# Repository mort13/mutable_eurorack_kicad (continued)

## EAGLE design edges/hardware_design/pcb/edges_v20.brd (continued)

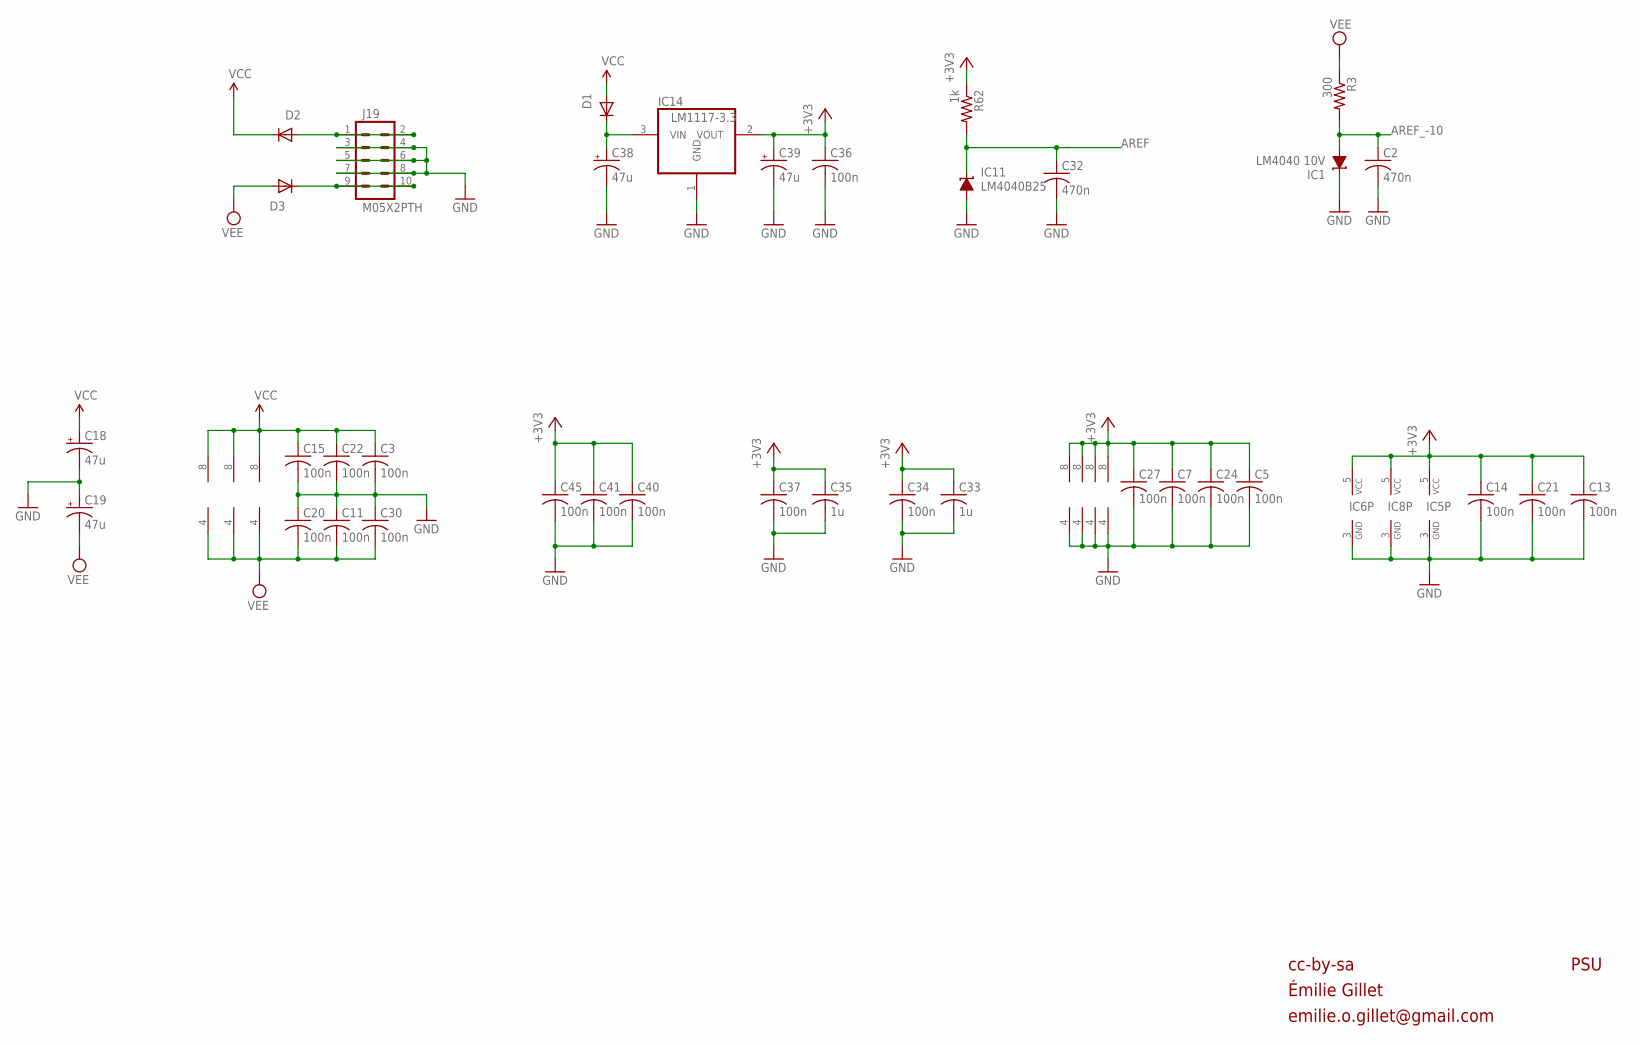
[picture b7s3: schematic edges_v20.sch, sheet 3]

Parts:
C2, C32: 470n; C0603
C3, C5, C7, C11, C13, C14, C15, C20, C21, C22, C24, C27, C30, C34, C36, C37, C40, C41, C45: 100n; C0603
C18, C19, C38, C39: 47u; PANASONIC_D
C33, C35: 1u; C0603
D1, D2, D3: 1N5819HW; SOD123
IC1: LM4040 10V; DBZ_R-PDSO-G3
IC2, IC7, IC9: TL072D; SO08
IC3, IC4, IC10, IC12: MCP6002; SO08
IC5: 74AHC1G125DBV; SOT23-5
IC6, IC8: 74AHC1G86DBV; SOT23-5
IC11: LM4040B25; DBZ_R-PDSO-G3
IC14: LM1117-3.3; SOT223
J19: M05X2PTH; AVR_ICSP
R3: 300; R0603
R62: 1k; R0603

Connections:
+3V3: C5.1, C7.1, C13.1, C14.1, C21.1, C24.1, C27.1, C33.1, C34.1, C35.1, C36.1, C37.1, C39.+, C40.1, C41.1, C45.1, IC3.8 (V+), IC4.8 (V+), IC5.5 (VCC), IC6.5 (VCC), IC8.5 (VCC), IC10.8 (V+), IC12.8 (V+), IC14.2 (VOUT), R62.1; also elsewhere on the board
AREF: C32.1, IC11.1 (C), R62.2; also elsewhere on the board
AREF_-10: C2.1, IC1.2 (A), R3.2; also elsewhere on the board
GND: C2.2, C3.2, C5.2, C7.2, C11.1, C13.2, C14.2, C15.2, C18.-, C19.+, C20.1, C21.2, C22.2, C24.2, C27.2, C30.1, C32.2, C33.2, C34.2, C35.2, C36.2, C37.2, C38.-, C39.-, C40.2, C41.2, C45.2, IC1.1 (C), IC3.4 (V-), IC4.4 (V-), IC5.3 (GND), IC6.3 (GND), IC8.3 (GND), IC10.4 (V-), IC11.2 (A), IC12.4 (V-), IC14.1 (GND), J19.3, J19.4, J19.5, J19.6, J19.7, J19.8; also elsewhere on the board
unnamed: C38.+, D1.C, IC14.3 (VIN)
unnamed: D2.A, J19.1, J19.2
unnamed: D3.C, J19.9, J19.10
VCC: C3.1, C15.1, C18.+, C22.1, D1.A, D2.C, IC2.8 (V+), IC7.8 (V+), IC9.8 (V+); also elsewhere on the board
VEE: C11.2, C19.-, C20.2, C30.2, D3.A, IC2.4 (V-), IC7.4 (V-), IC9.4 (V-), R3.1

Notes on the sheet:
cc-by-sa
PSU
Émilie Gillet
emilie.o.gillet@gmail.com

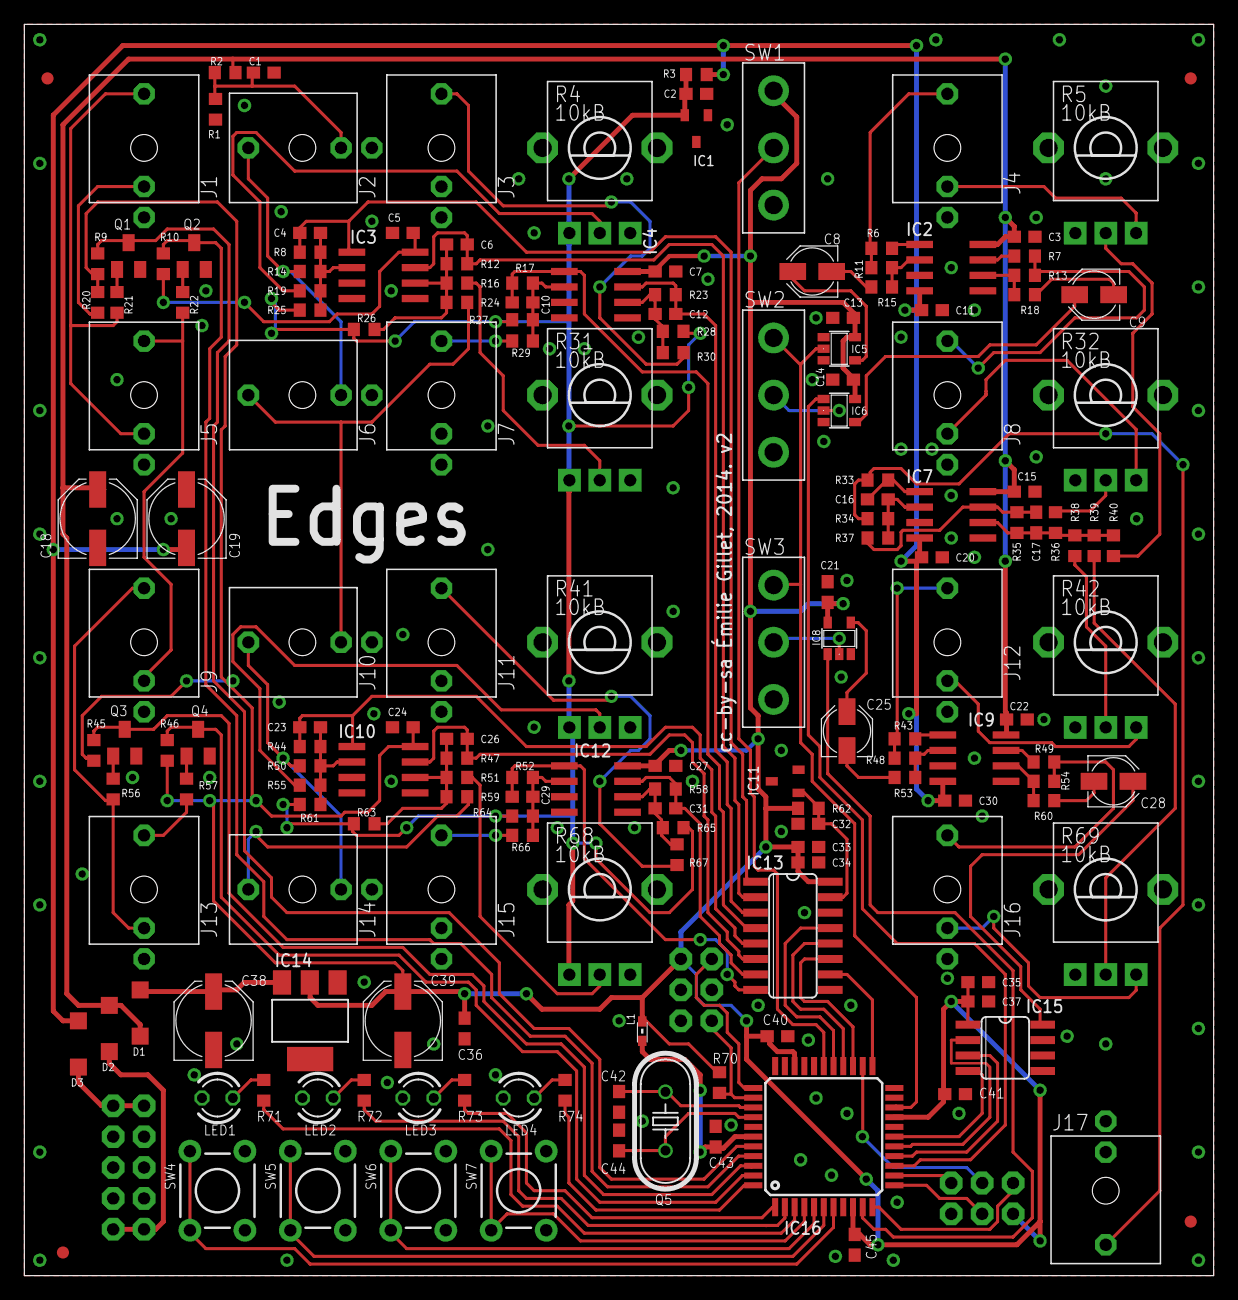
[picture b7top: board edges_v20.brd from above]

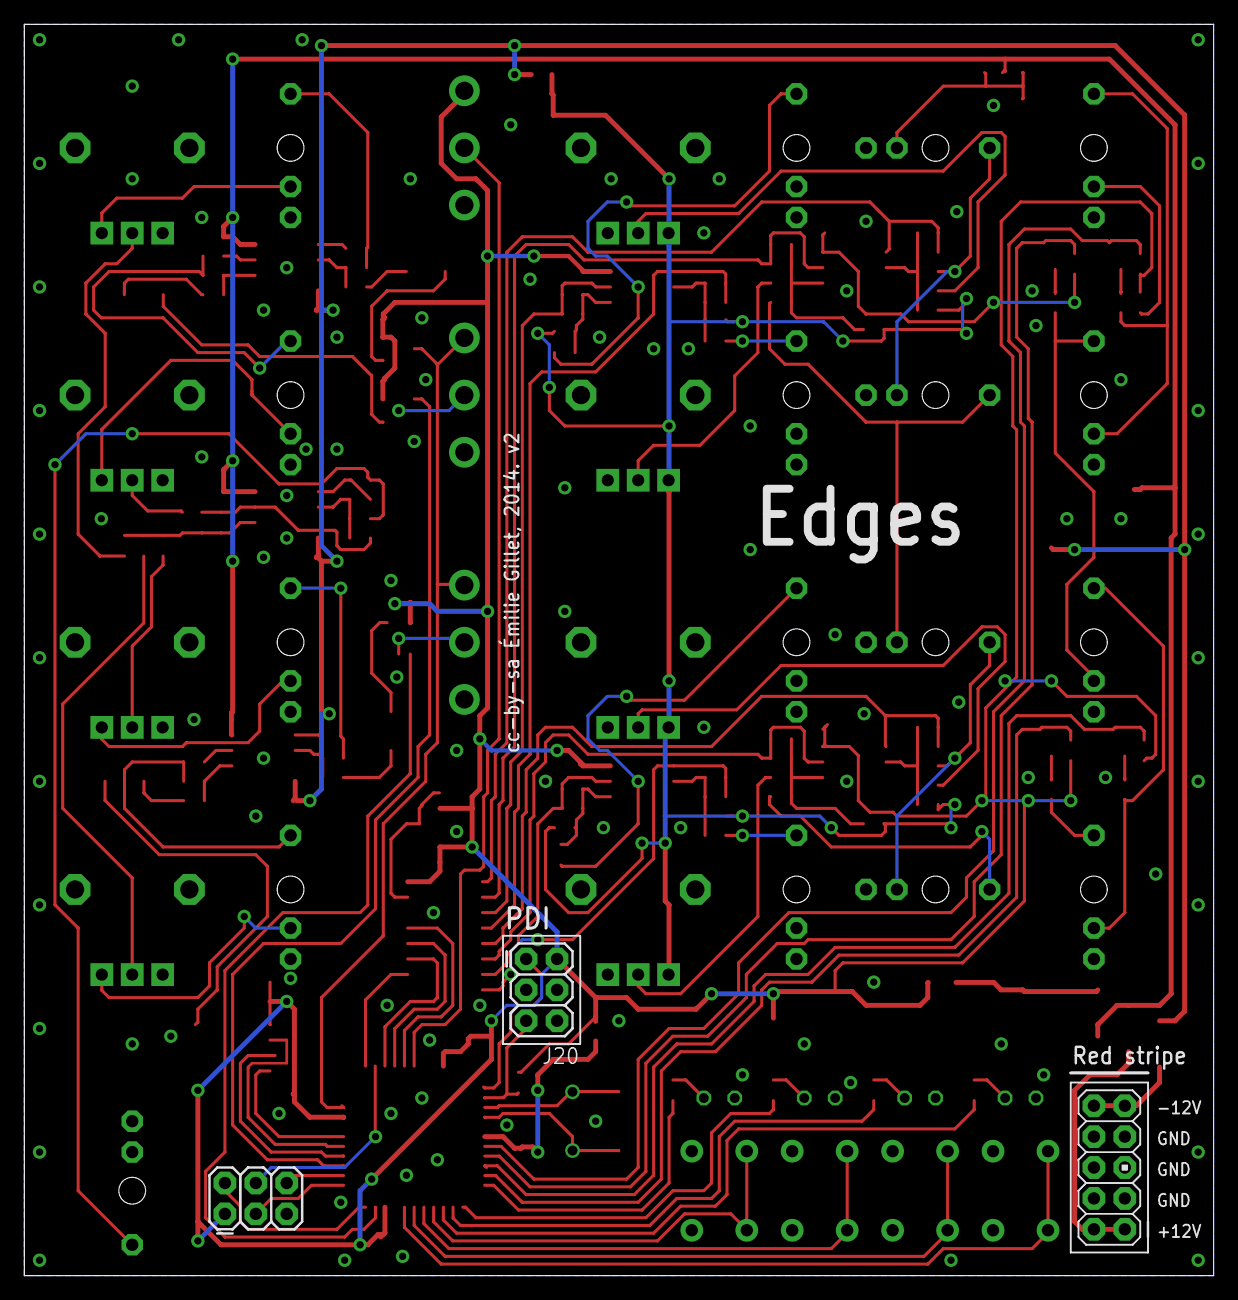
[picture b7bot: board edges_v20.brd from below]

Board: 2 copper layers, 97.8 x 102.9 mm, 179 parts (3 on the bottom side), 118 nets.

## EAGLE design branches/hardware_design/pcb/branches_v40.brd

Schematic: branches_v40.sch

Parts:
C1, C4, C6, C7, C8: 100n; C0603
C2, C5: 1n; C0603
C3, C9: 22u; PANASONIC_C
D1: 1N5819HW; SOD123
F1, F2, F3, F4: FIDUCIAL1X2; FIDUCIAL-1X2
IC1: LM4040 5.0V; DBZ_R-PDSO-G3
IC2: LM1117-5.0; SOT223
IC3: MCP6002; SO08
IC4: ATMEGA88PA-AU; TQFP32-08
J1, J2, J3, J4, J5, J6, J7, J8: PJ301_THONKICONN6; WQP_PJ_301M6
J9: AVR_SPI_PRG_6PTH; 2X3
J10: M05X2PTH; AVR_ICSP
L1: WE-CBF_0603; 0603
LED1, LED2: WP937EGW; LED3MM
Q1, Q2: MMBT3904; SOT23-BEC
R1, R2, R14: 10k; R0603
R3, R4, R5, R7, R8, R9, R10, R18: 100k; R0603
R6, R15: 10kB; ALPS_POT_VERTICAL_PS
R11, R19: 220; R0603
R12, R13, R16, R17: 1.0k; R0603
SW1, SW2: TAC_SWITCHPTH; TACTILE-PTH

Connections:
+5V: C1.1, C3.+, C4.1, C6.1, IC2.2 (VOUT), IC3.8 (V+), IC4.4 (VCC), IC4.6 (VCC), J9.2, L1.1, R14.2
AREF: C7.1, IC4.20 (AREF)
GATE1_IN: J1.P3 (3), J5.P2 (2), R10.2
GATE2_IN: J5.P3 (3), R18.2
GND: C1.2, C3.-, C4.2, C6.2, C7.2, C8.2, C9.-, IC1.1 (C), IC2.1 (GND), IC3.3 (+IN), IC3.4 (V-), IC3.5 (+IN), IC4.3 (GND), IC4.5 (AGND), IC4.21 (GND), J1.P1 (1), J1.P2 (2), J2.P1 (1), J3.P1 (1), J4.P1 (1), J5.P1 (1), J6.P1 (1), J7.P1 (1), J8.P1 (1), J9.6, J10.3, J10.4, J10.5, J10.6, J10.7, J10.8, Q1.E, Q2.E, R6.P$1 (E), R15.P$1 (E), SW1.1, SW1.2, SW2.1, SW2.2
IN1: IC4.2 (PD4(XCK/T0)), Q1.C
IN2: IC4.11 (PD7(AIN1)), Q2.C
MISO: IC4.16 (PB4(MISO)), J9.1
MOSI: IC4.15 (PB3(MOSI/OC2)), J9.4
unnamed: Q1.B, R10.1
unnamed: Q2.B, R18.1
unnamed: D1.A, J10.1
unnamed: C5.1, IC3.2 (-IN), R7.2, R8.2, R9.1
unnamed: J8.P3 (3), R16.2
unnamed: R7.1, R15.P$2 (S)
unnamed: R3.1, R6.P$2 (S)
unnamed: J2.P3 (3), R5.1
unnamed: J6.P3 (3), R8.1
unnamed: IC4.31 (PD1(TXD)), R11.1
unnamed: LED1.A, R11.2
unnamed: IC4.32 (PD2(INT0)), LED1.K (C)
unnamed: IC4.13 (PB1(OC1A)), LED2.A
unnamed: LED2.K (C), R19.1
unnamed: IC4.12 (PB0(ICP)), R19.2
unnamed: C2.1, IC3.6 (-IN), R3.2, R4.1, R5.2
unnamed: J3.P3 (3), R13.2
unnamed: J4.P3 (3), R12.2
unnamed: J7.P3 (3), R17.2
unnamed: C8.1, IC4.18 (AVCC), L1.2
OUT1_A: IC4.1 (PD3(INT1)), R13.1
OUT1_B: IC4.30 (PD0(RXD)), R12.1
OUT2_A: IC4.10 (PD6(AIN0)), R17.1
OUT2_B: IC4.9 (PD5(T1)), R16.1
P1_CV: C2.2, IC3.7 (OUT), IC4.24 (PC1(ADC1)), R4.2
P2_CV: C5.2, IC3.1 (OUT), IC4.23 (PC0(ADC0)), R9.2
REF_-5: IC1.2 (A), R1.2, R2.2, R6.P$3 (A), R15.P$3 (A)
RESET: IC4.29 (PC6(/RESET)), J9.5, R14.1
SCK: IC4.17 (PB5(SCK)), J9.3
SW1: IC4.26 (PC3(ADC3)), SW1.3, SW1.4
SW2: IC4.25 (PC2(ADC2)), SW2.3, SW2.4
VCC: C9.+, D1.C, IC2.3 (VIN)
VEE: J10.9, J10.10, R1.1, R2.1

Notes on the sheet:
cc-by-sa
Branches
Wurth 742792693
Émilie Gillet
emilie.o.gillet@gmail.com

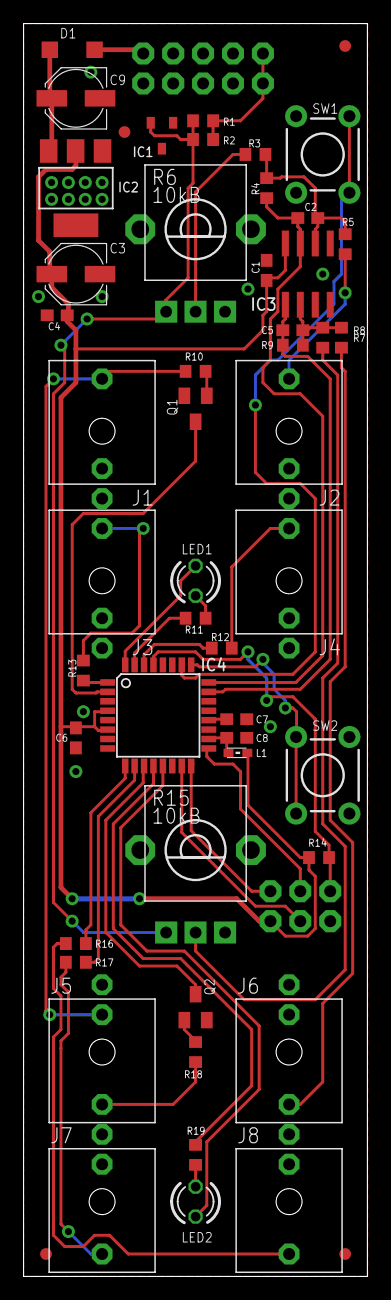
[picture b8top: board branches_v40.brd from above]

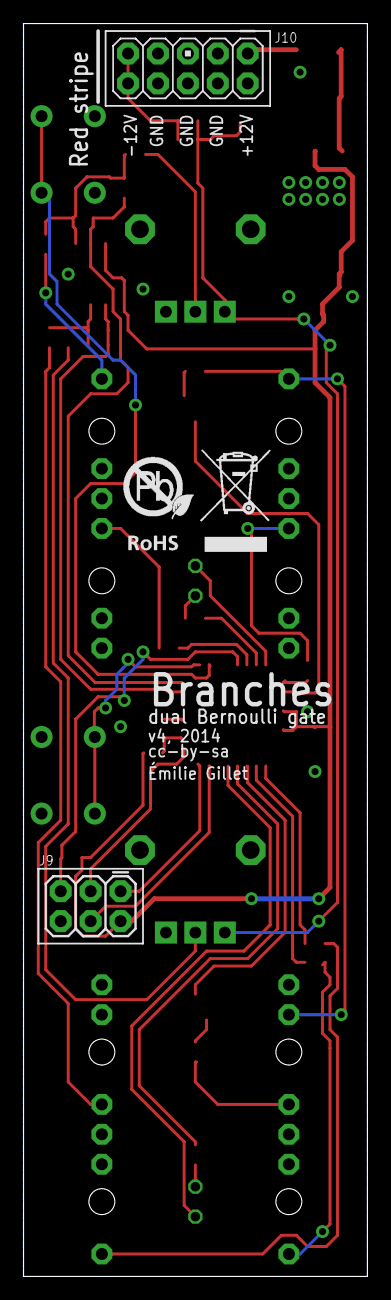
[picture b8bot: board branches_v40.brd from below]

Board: 2 copper layers, 29.2 x 106.4 mm, 55 parts (3 on the bottom side), 42 nets.

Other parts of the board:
U$1: ROHS

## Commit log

2020-03-23 Updated README for fork; XML conversions
2020-03-23 add KiCad stuff
2020-03-23 KiCad ears
2020-03-23 KiCad
2020-09-01 Some KiCad imports
2020-09-16 Clouds KiCad import
2020-10-09 Veils KiCad import
2022-06-13 elements KiCad import
2022-06-13 KiCad imports
2022-07-03 Can no longer supply XML versions
2023-01-11 clouds import etc.
2023-05-24 Re-imports
2023-07-31 Redo Ears
2023-07-31 .gitignore update, add lib tables and caches
